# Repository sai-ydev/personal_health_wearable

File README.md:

# Wearable for Personal Health Monitoring
 
This is the repository for the Personal Health Monitoring Wearable. 

Here is the folder structure:
- **nRF54L15 Design Files** contains design files based on the nRF54L15 SoC. This couldn't be executed because of lack of availability.
- **BL54L15 Design Files** contains design files based on the BL54L15 module from [Ezurio](https://www.ezurio.com/product/bl54l15-series-bluetooth-le-80215-4-nfc).

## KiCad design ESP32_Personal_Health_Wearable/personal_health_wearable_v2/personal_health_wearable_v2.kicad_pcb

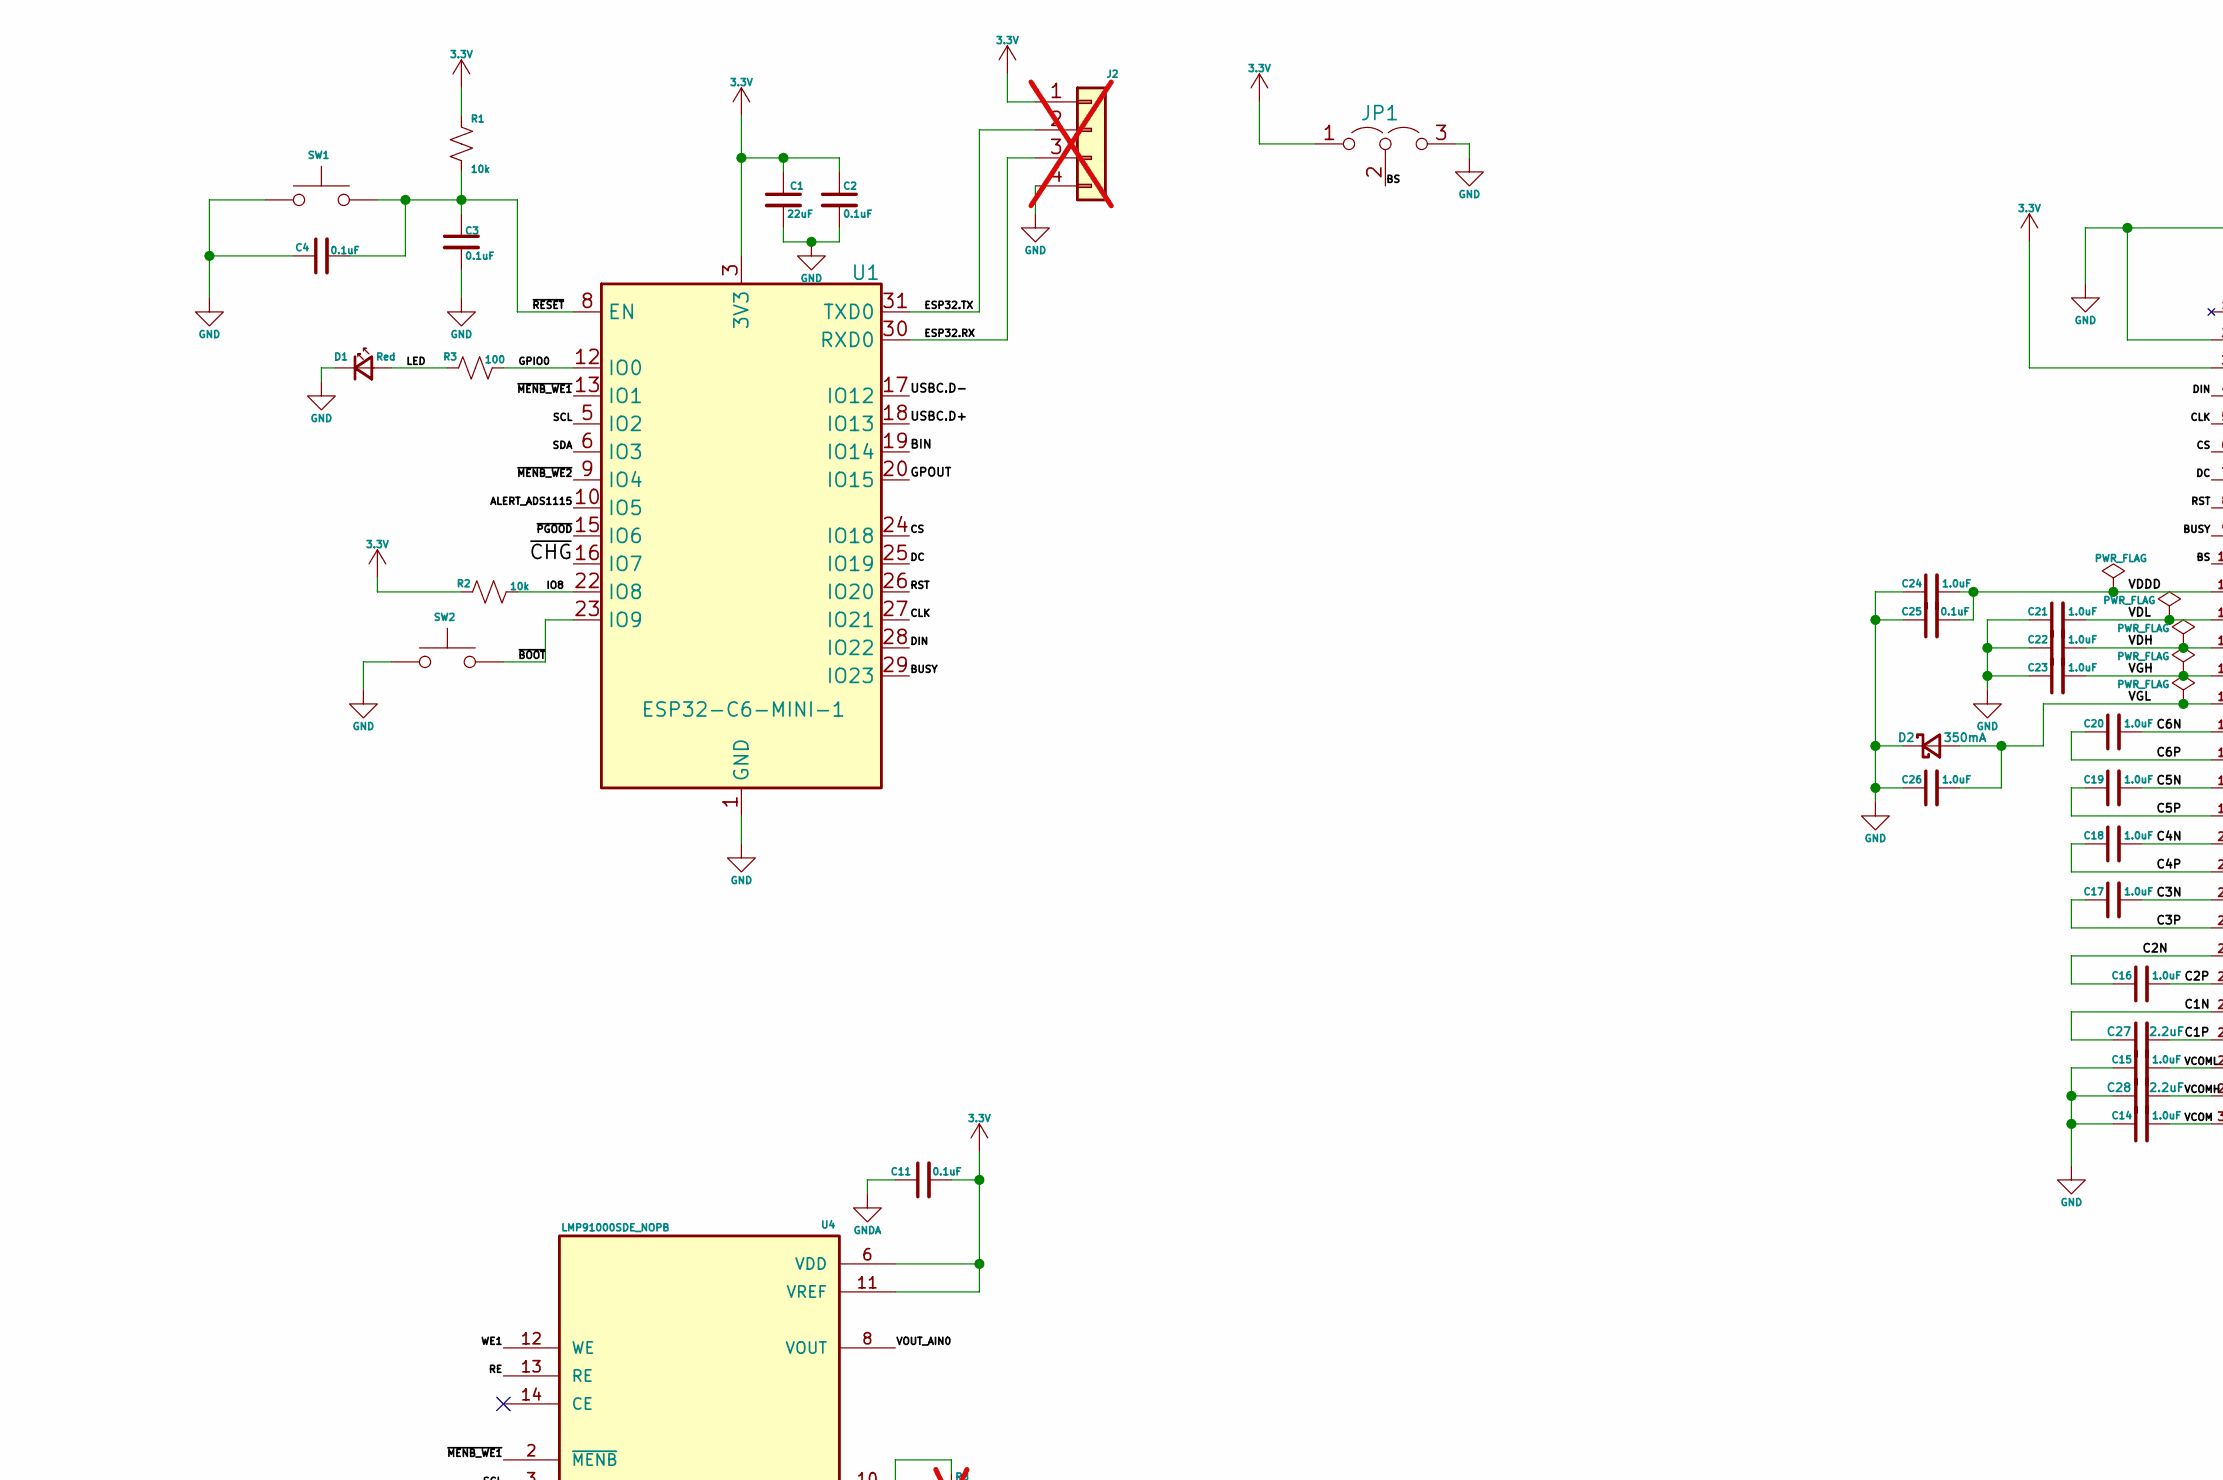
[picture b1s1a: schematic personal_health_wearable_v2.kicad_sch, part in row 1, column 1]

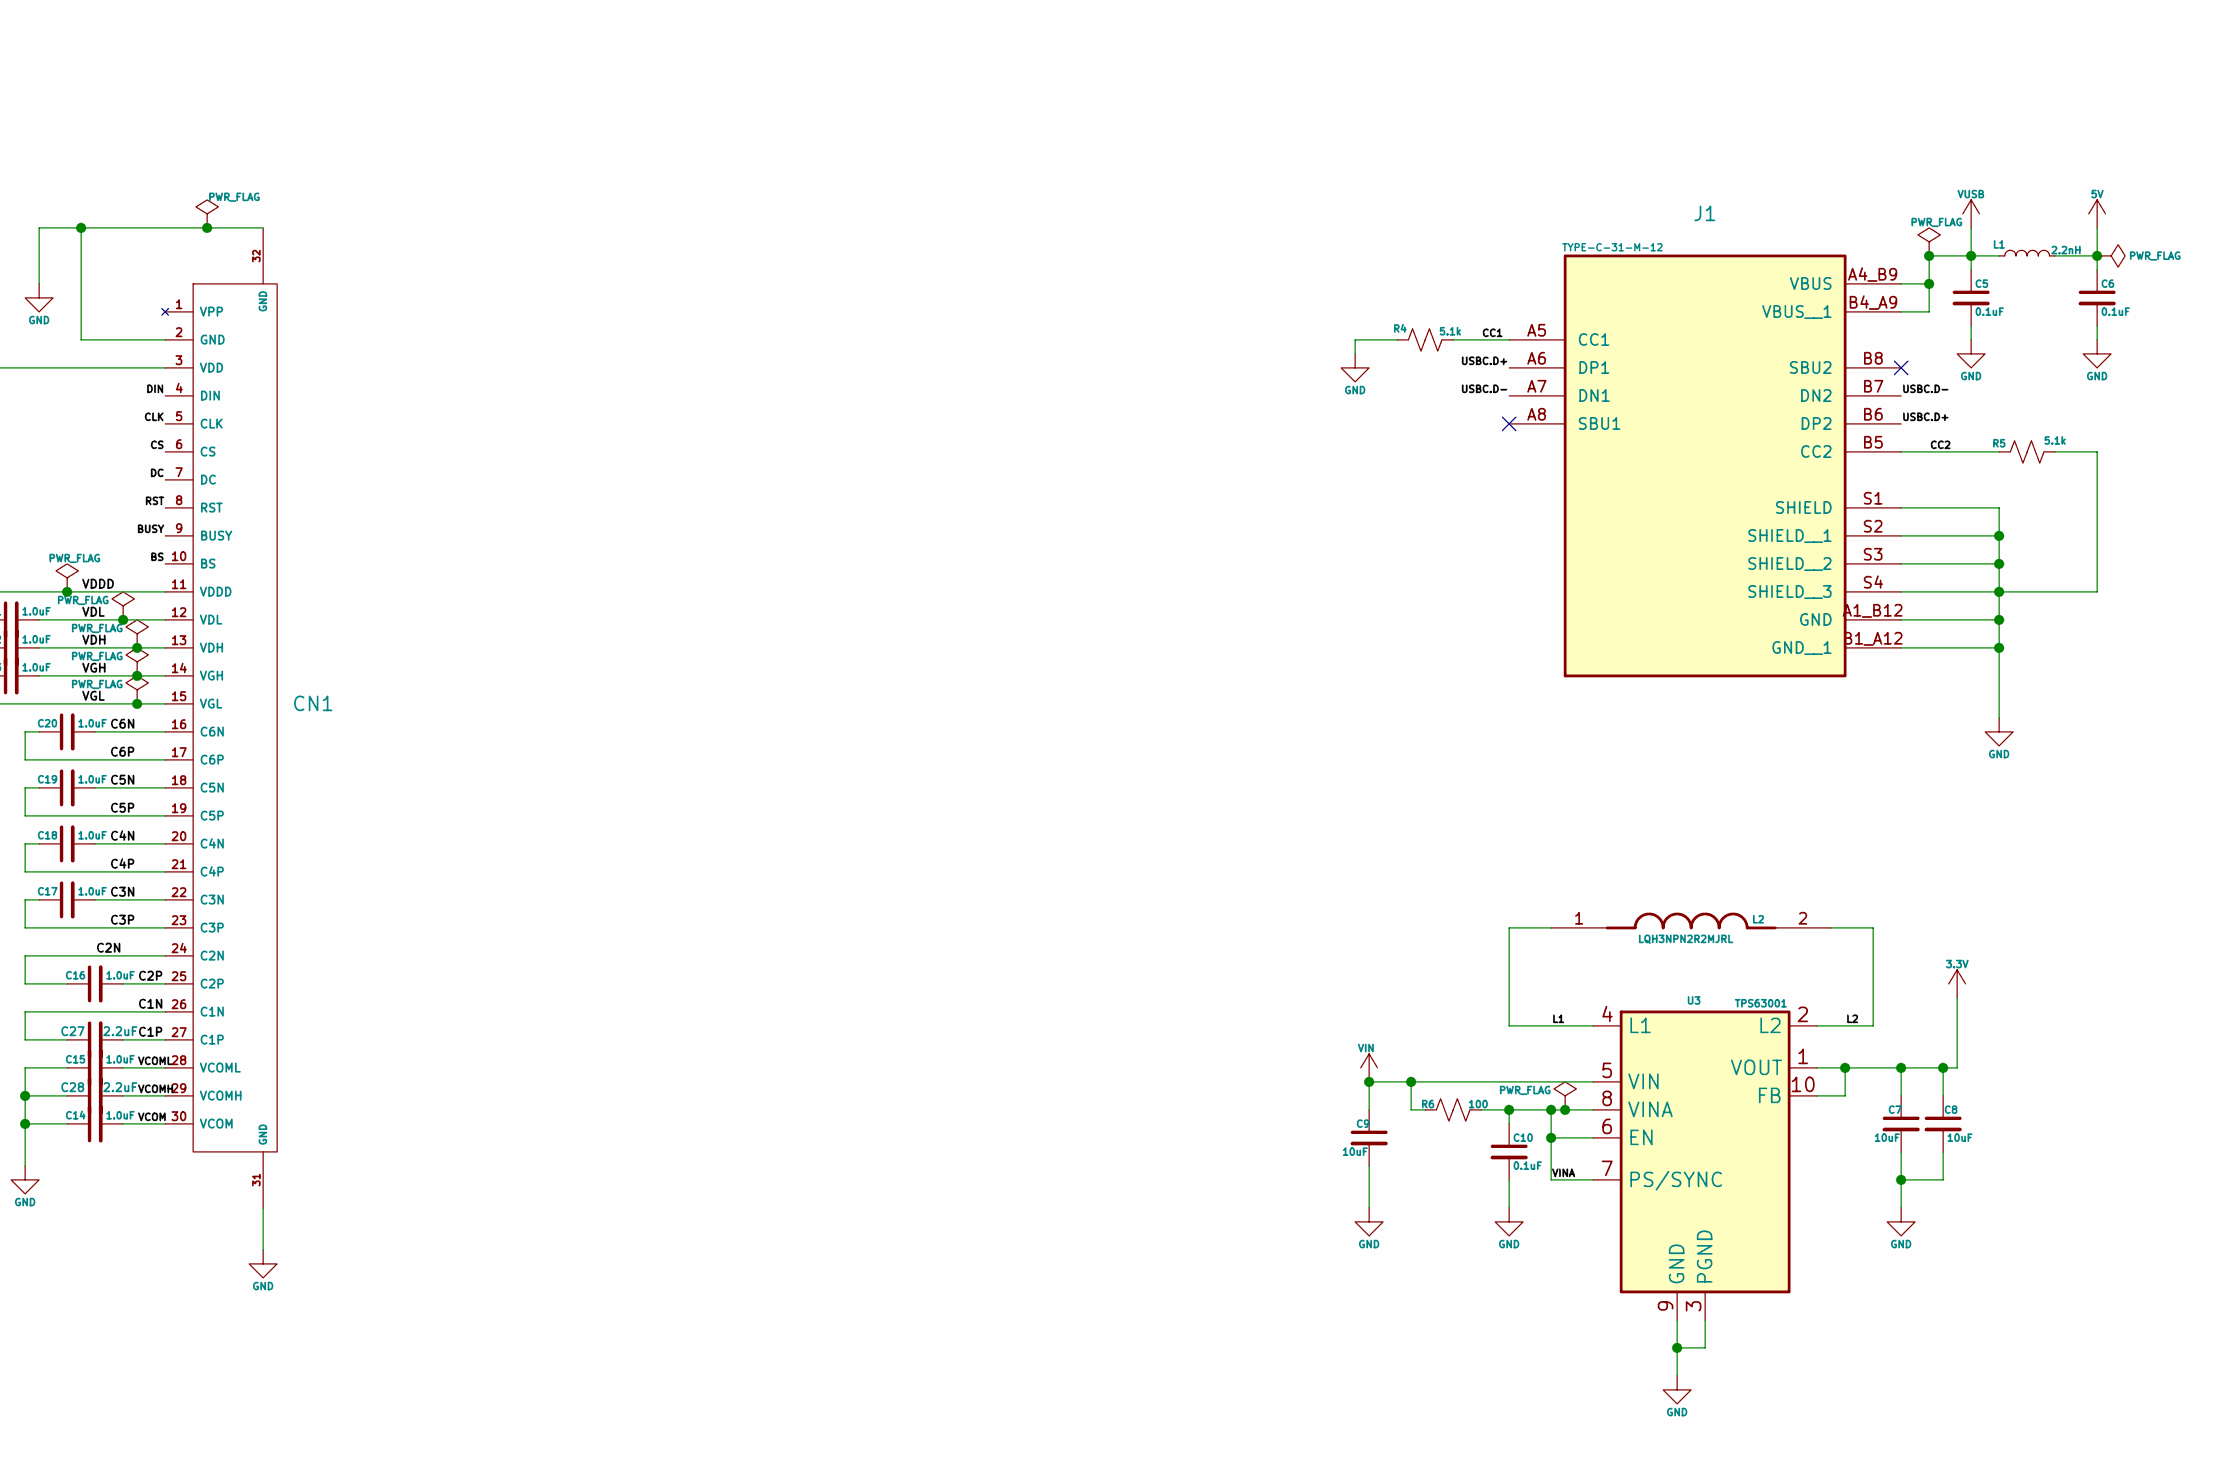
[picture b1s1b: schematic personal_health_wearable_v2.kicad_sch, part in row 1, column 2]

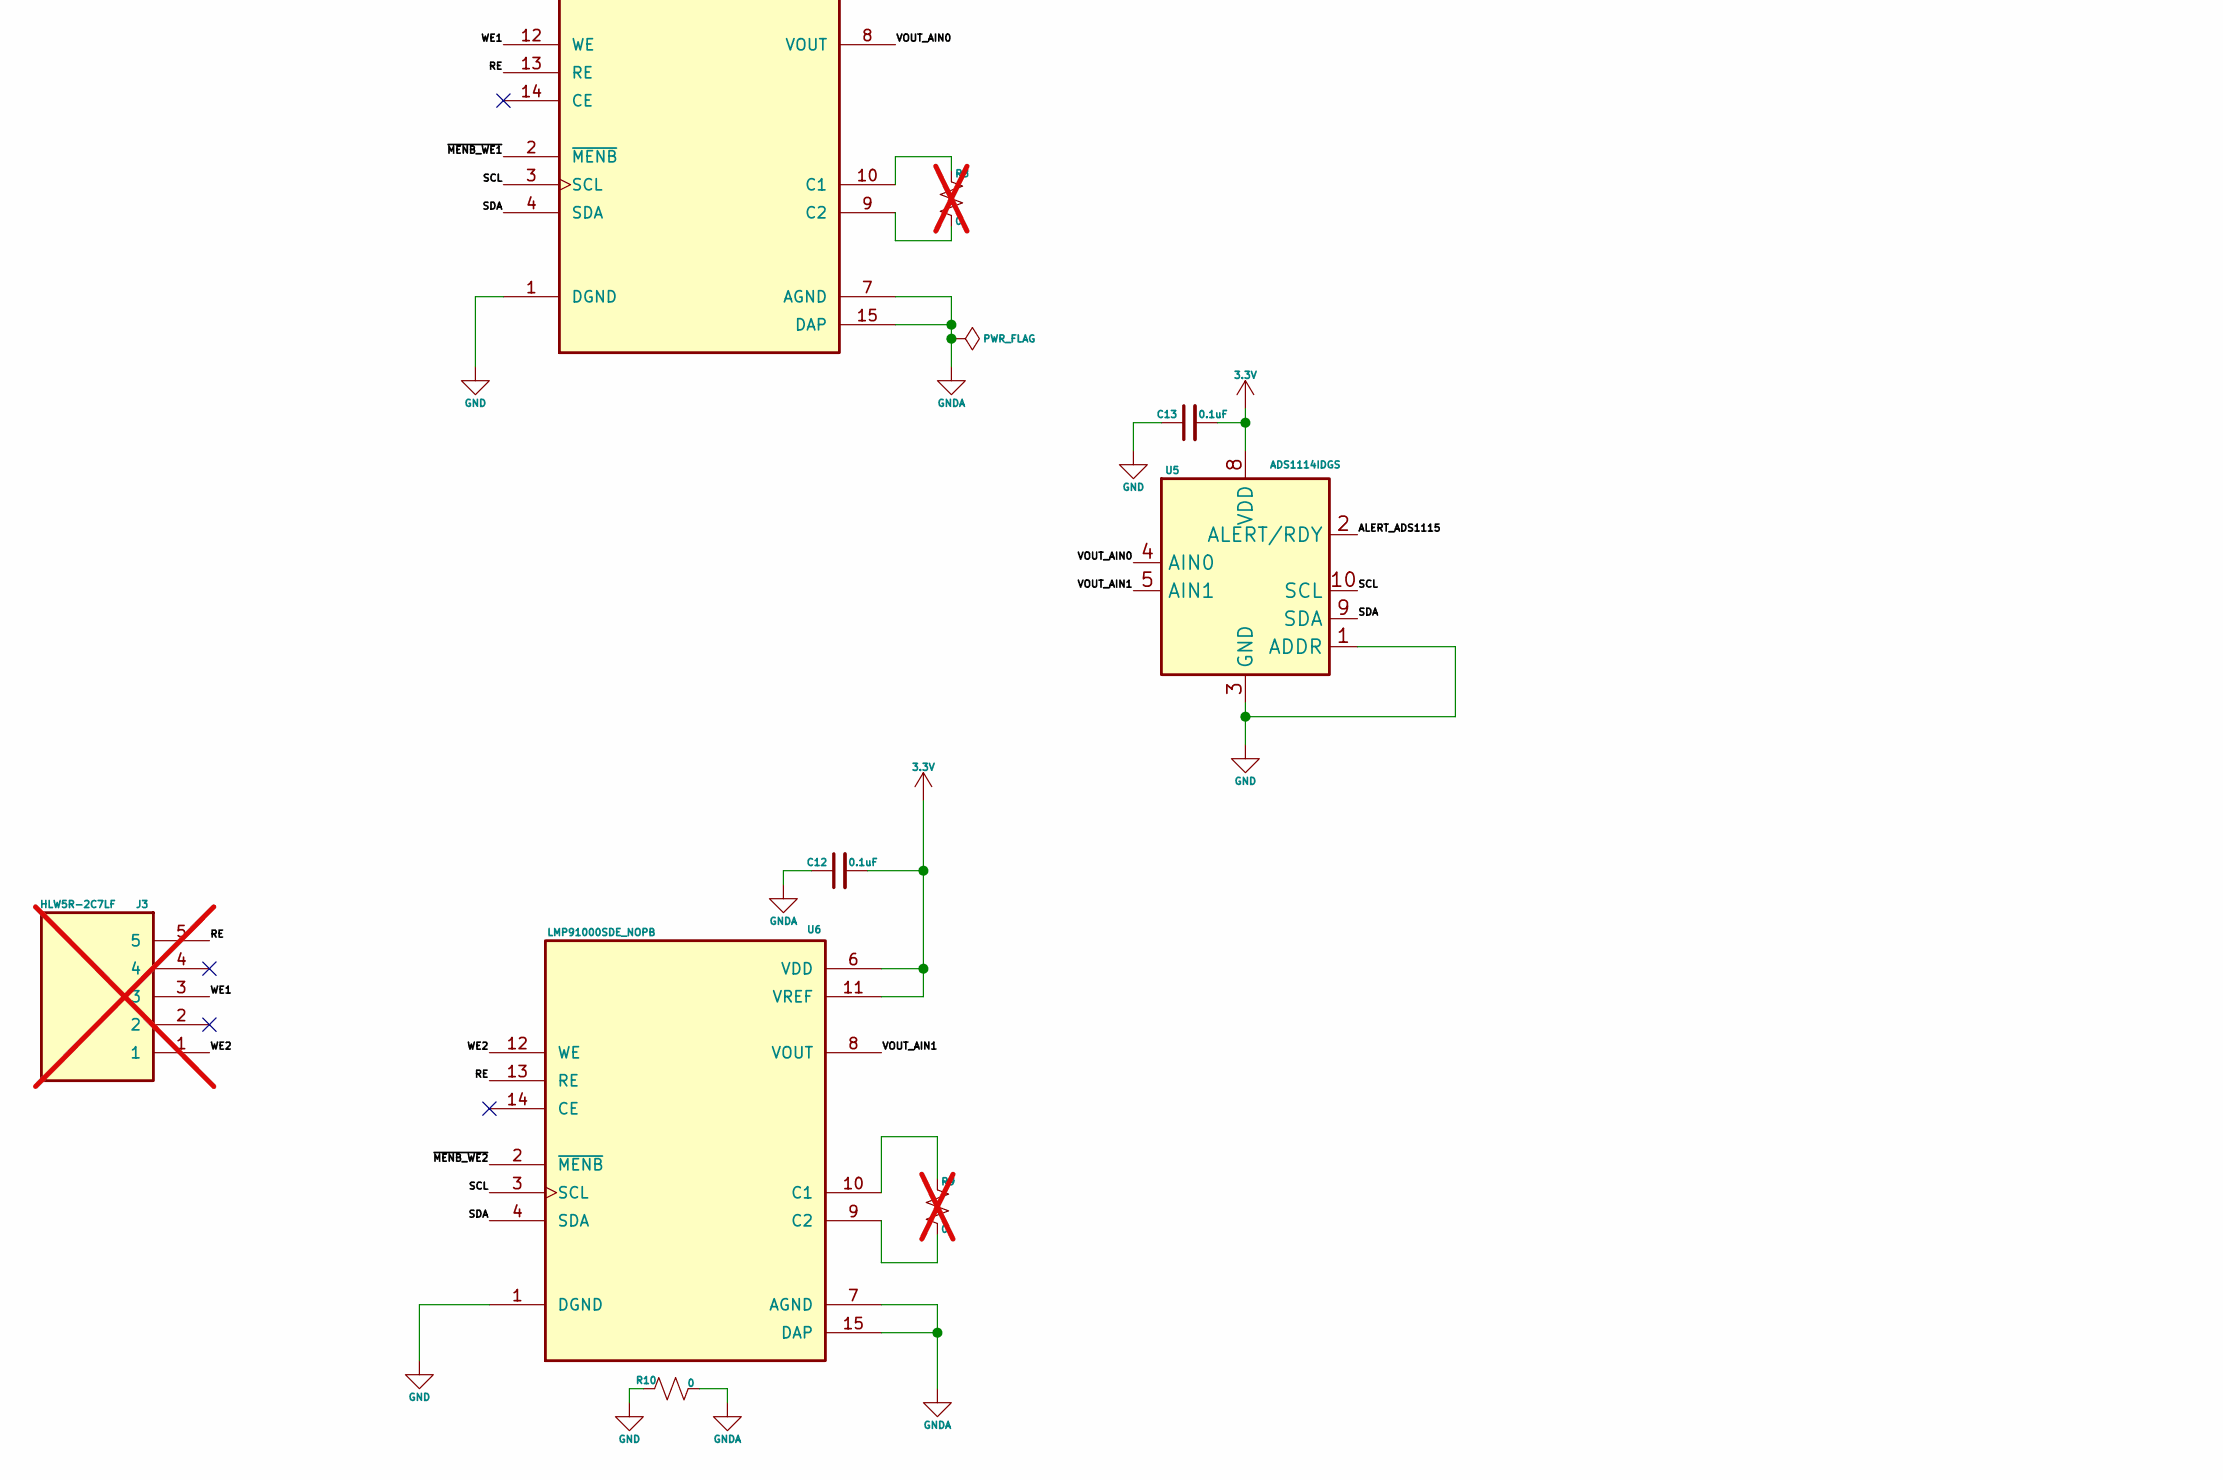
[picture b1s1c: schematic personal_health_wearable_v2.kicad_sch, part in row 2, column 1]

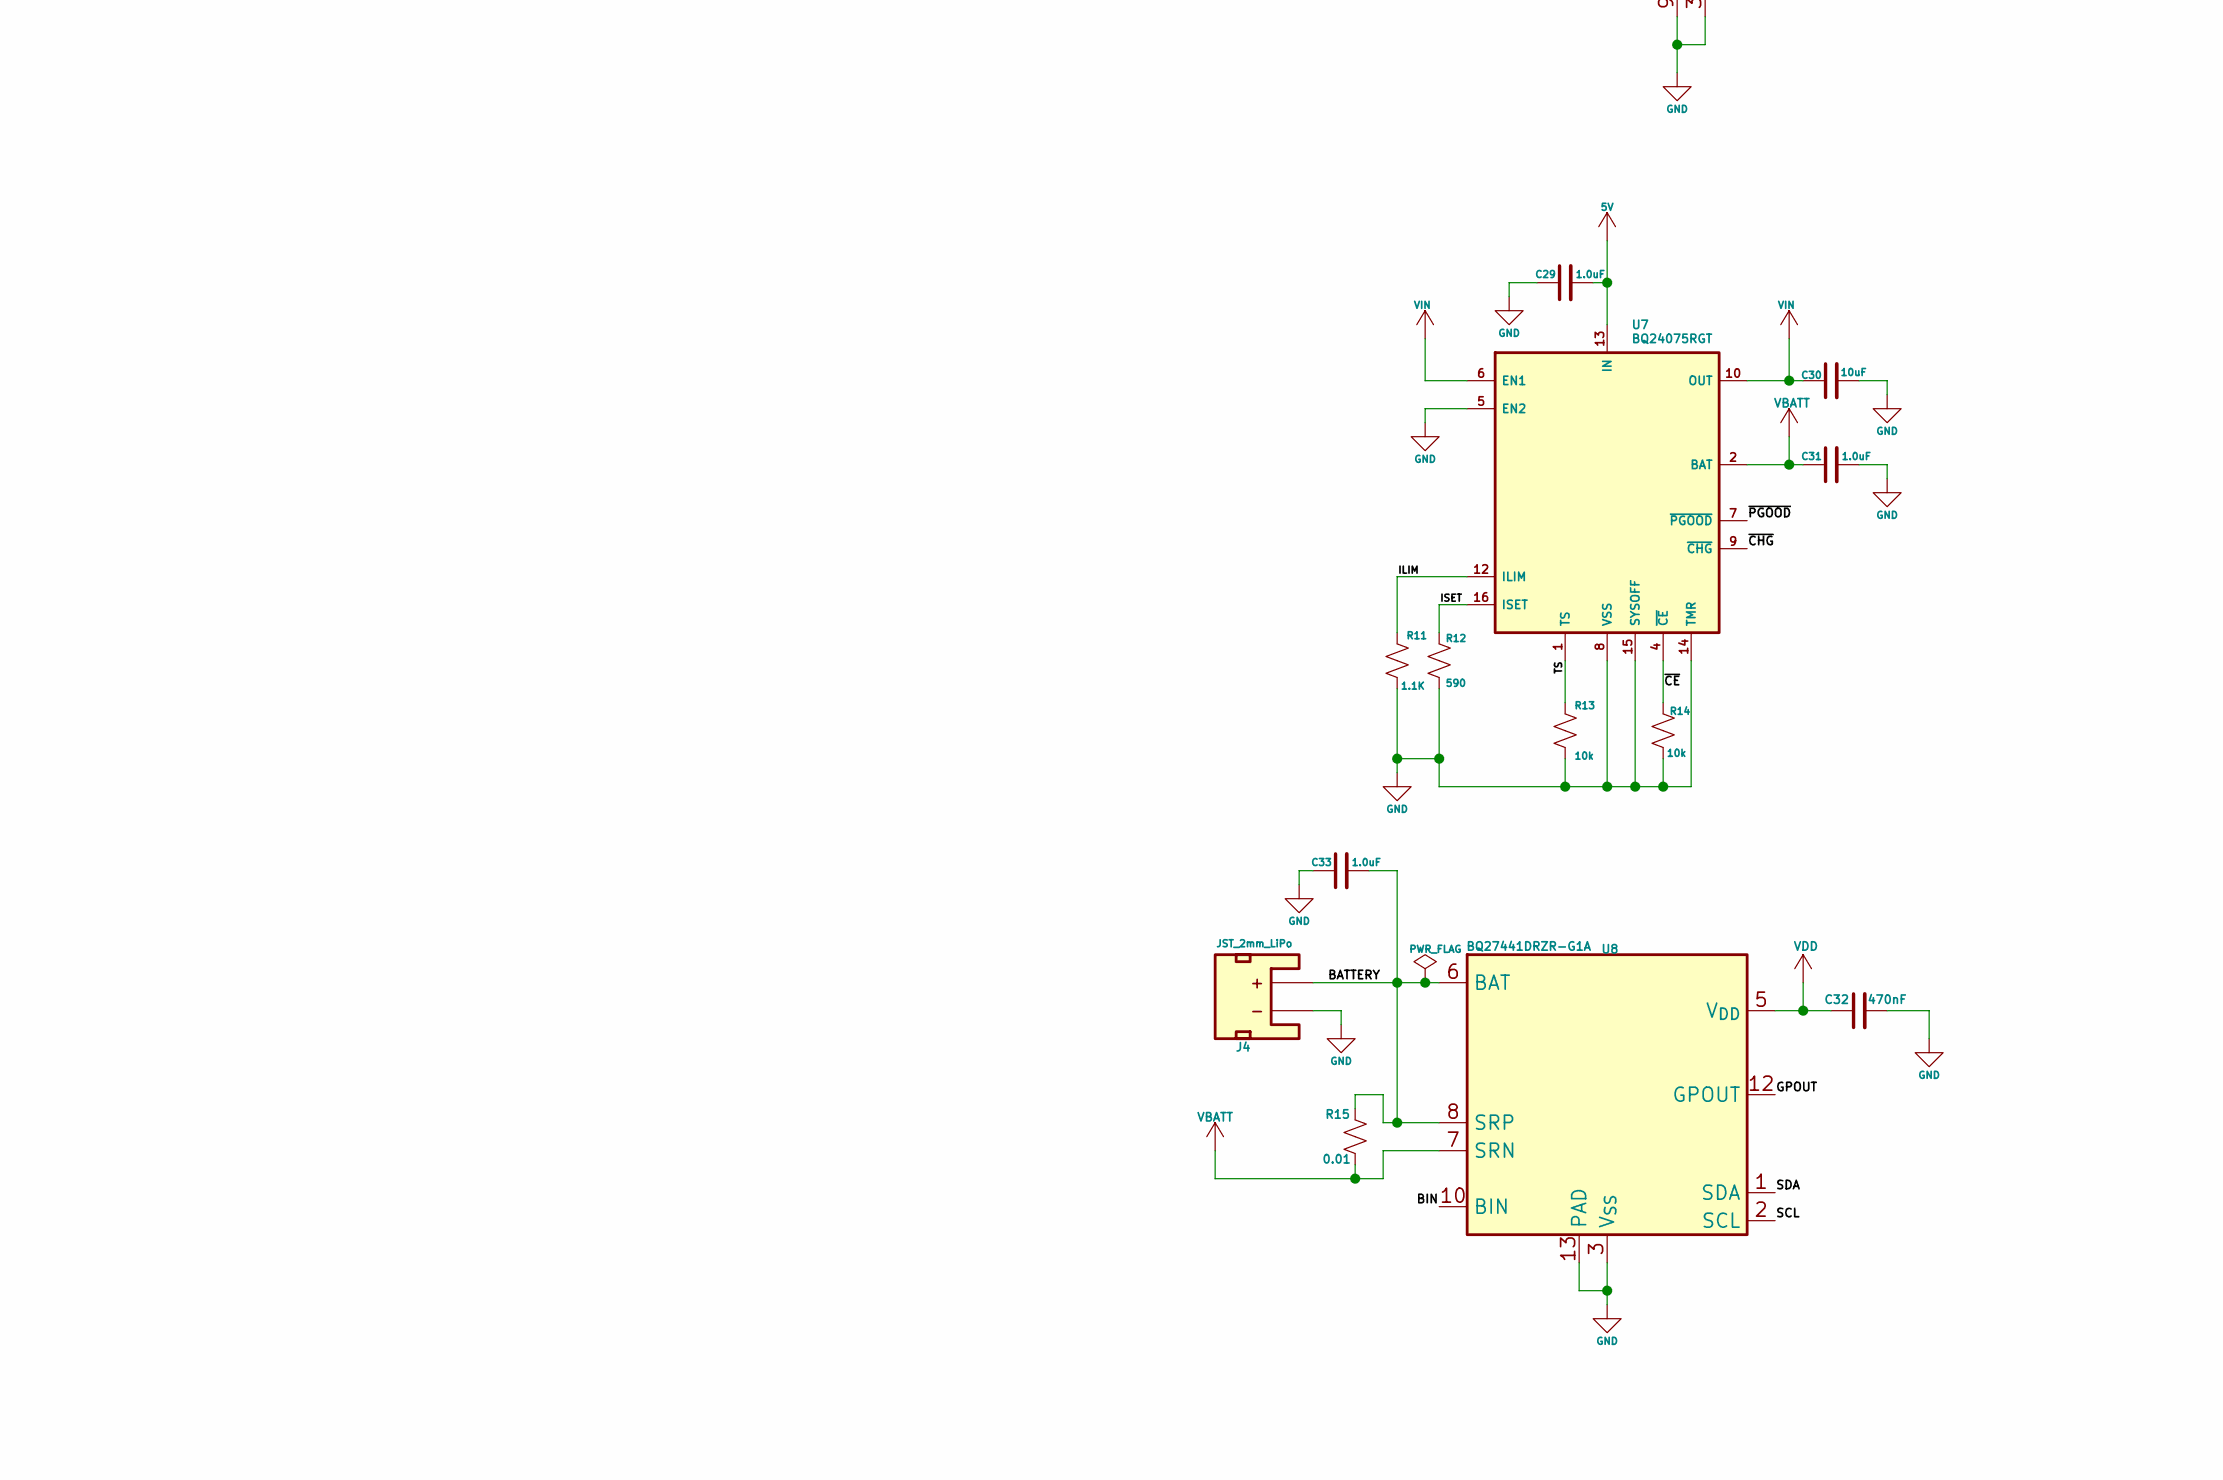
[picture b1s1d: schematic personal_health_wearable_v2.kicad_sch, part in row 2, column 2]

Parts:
C1: 22uF; C_0402_1005Metric; Voltage 6.3V; Tolerance 20%; LCSC C105226
C2, C3, C4, C5, C6, C10, C11, C12, C13, C25: 0.1uF; C_0402_1005Metric; Voltage 6.3V; Tolerance 10%; LCSC C1525
C7, C8, C9, C30: 10uF; C_0402_1005Metric; Voltage 6.3V; Tolerance 20%; LCSC C15525
C14, C15, C16, C17, C18, C19, C20, C21, C22, C23, C24, C26, C29, C31, C33: 1.0uF; C_0402_1005Metric; Voltage 16V; Tolerance 10%; LCSC C361059
C27, C28: 2.2uF; C_0402_1005Metric; Voltage 10V; Tolerance 10%; LCSC C159814
C32: 470nF; C_0402_1005Metric; Voltage 6.3V; Tolerance 10%; LCSC C47339
CN1: FPC-SMD_30P-P0.50_FH12A-30S-0.5SH; Manufacturer Part FH12A-30S-0.5SH(55); LCSC C3036214
D1: Red; LED_0402_1005Metric_Red; LCSC C74341
D2: 350mA; D_SOD-523; LCSC C154768
J1: TYPE-C-31-M-12; HRO_TYPE-C-31-M-12; PARTREV 2020.12.08; LCSC C165948
J2: Conn_01x04_RA; 1x04_P2.54mm_Header_Horizontal_SMD; not fitted
J3: HLW5R-2C7LF; AMPHENOL_HLW5R-2C7LF; PARTREV C; DigiKey_Part_Number 609-1816-ND; not fitted
J4: JST_2mm_LiPo; JST_1x02_P2.0mm_Horizontal_SMD; LCSC C295747
JP1: Jumper_3_Open; Jumper_3_NO
L1: 2.2nH; L_0402_1005Metric; LCSC C27122
L2: LQH3NPN2R2MJRL; IND_LQH3NPN2R2MJRL; PARTREV N/A; LCSC C341775
R1, R2, R13, R14: 10k; R_0402_1005Metric; LCSC C25531
R3, R6: 100; R_0402_1005Metric; LCSC C25076
R4, R5: 5.1k; R_0402_1005Metric; LCSC C25905
R8, R9: 0; R_0402_1005Metric; not fitted
R10: 0; R_0402_1005Metric; LCSC C17168
R11: 1.1K; R_0402_1005Metric; LCSC C25860
R12: 590; R_0402_1005Metric; LCSC C159007
R15: 0.01; R_0402_1005Metric; LCSC C346478
SW1, SW2: SMD_4.6x2.8mm_h1.9mm; Push_SMD_4.6x2.8mm_h1.9mm; LCSC C99271
U1: ESP32-C6-MINI-1; LCSC C5736265
U3: TPS63001; Texas_DRC0010J_ThermalVias; LCSC C28060
U4, U6: LMP91000SDE_NOPB; SON50P400X400X80-15N; PARTREV DEC 2014; LCSC C181364
U5: ADS1114IDGS; TSSOP-10_3x3mm_P0.5mm; LCSC C174291
U7: BQ24075RGT; VQFN-16-1EP_3x3mm_P0.5mm_EP1.6x1.6mm; LCSC C15464
U8: BQ27441DRZR-G1A; Texas_S-PDSO-N12; LCSC C473397

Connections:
3.3V: C1.1, C2.1, C7.1, C8.1, C11.2, C12.2, C13.2, CN1.3 (VDD), J2.1, JP1.1 (A), R1.2, R2.2, U1.3 (3V3), U3.1 (VOUT), U3.10 (FB), U4.6 (VDD), U4.11 (VREF), U5.8 (VDD), U6.6 (VDD), U6.11 (VREF)
5V: C6.1, C29.2, L1.2, U7.13 (IN)
/ALERT_ADS1115: U1.10 (IO5), U5.2 (ALERT/RDY)
/BATTERY: C33.2, J4.2 (+), R15.2, U8.6 (BAT), U8.8 (SRP)
/BIN: U1.19 (IO14), U8.10 (BIN)
/BS: CN1.10 (BS), JP1.2 (C)
/BUSY: CN1.9 (BUSY), U1.29 (IO23)
/C1N: C27.1, CN1.26 (C1N)
/C1P: C27.2, CN1.27 (C1P)
/C2N: C16.1, CN1.24 (C2N)
/C2P: C16.2, CN1.25 (C2P)
/C3N: C17.2, CN1.22 (C3N)
/C3P: C17.1, CN1.23 (C3P)
/C4N: C18.2, CN1.20 (C4N)
/C4P: C18.1, CN1.21 (C4P)
/C5N: C19.2, CN1.18 (C5N)
/C5P: C19.1, CN1.19 (C5P)
/C6N: C20.2, CN1.16 (C6N)
/C6P: C20.1, CN1.17 (C6P)
/CC1: J1.A5 (CC1), R4.2
/CC2: J1.B5 (CC2), R5.1
/CLK: CN1.5 (CLK), U1.27 (IO21)
/CS: CN1.6 (CS), U1.24 (IO18)
/DC: CN1.7 (DC), U1.25 (IO19)
/DIN: CN1.4 (DIN), U1.28 (IO22)
/ESP32.RX: J2.3, U1.30 (RXD0)
/ESP32.TX: J2.2, U1.31 (TXD0)
/GPIO0: R3.2, U1.12 (IO0)
/GPOUT: U1.20 (IO15), U8.12 (GPOUT)
/ILIM: R11.2, U7.12 (ILIM)
/IO8: R2.1, U1.22 (IO8)
/ISET: R12.2, U7.16 (ISET)
/L1: L2.1, U3.4 (L1)
/L2: L2.2, U3.2 (L2)
/LED: D1.2 (A), R3.1
/RE: J3.5, U4.13 (RE), U6.13 (RE)
/RST: CN1.8 (RST), U1.26 (IO20)
/SCL: U1.5 (IO2), U4.3 (SCL), U5.10 (SCL), U6.3 (SCL), U8.2 (SCL)
/SDA: U1.6 (IO3), U4.4 (SDA), U5.9 (SDA), U6.4 (SDA), U8.1 (SDA)
/TS: R13.2, U7.1 (TS)
/USBC.D+: J1.A6 (DP1), J1.B6 (DP2), U1.18 (IO13)
/USBC.D-: J1.A7 (DN1), J1.B7 (DN2), U1.17 (IO12)
/VCOM: C14.2, CN1.30 (VCOM)
/VCOMH: C28.2, CN1.29 (VCOMH)
/VCOML: C15.2, CN1.28 (VCOML)
/VDDD: C24.2, C25.2, CN1.11 (VDDD)
/VDH: C22.2, CN1.13 (VDH)
/VDL: C21.2, CN1.12 (VDL)
/VGH: C23.2, CN1.14 (VGH)
/VGL: C26.2, CN1.15 (VGL), D2.2 (A)
/VINA: C10.1, R6.2, U3.6 (EN), U3.7 (PS/SYNC), U3.8 (VINA)
/VOUT_AIN0: U4.8 (VOUT), U5.4 (AIN0)
/VOUT_AIN1: U5.5 (AIN1), U6.8 (VOUT)
/WE1: J3.3, U4.12 (WE)
/WE2: J3.1, U6.12 (WE)
/~BOOT: SW2.2, U1.23 (IO9)
/~CE: R14.2, U7.4 (~CE)
/~CHG: U1.16 (IO7), U7.9 (~CHG)
/~MENB_WE1: U1.13 (IO1), U4.2 (~MENB)
/~MENB_WE2: U1.9 (IO4), U6.2 (~MENB)
/~PGOOD: U1.15 (IO6), U7.7 (~PGOOD)
/~RESET: C3.1, C4.2, R1.1, SW1.2, U1.8 (EN)
GND: C1.2, C2.2, C3.2, C4.1, C5.2, C6.2, C7.2, C8.2, C9.2, C10.2, C13.1, C14.1, C15.1, C21.1, C22.1, C23.1, C24.1, C25.1, C26.1, C28.1, C29.1, C30.2, C31.2, C32.2, C33.1, CN1.2 (GND), CN1.31 (GND), CN1.32 (GND), D1.1 (K), D2.1 (K), J1.A1_B12 (GND), J1.B1_A12 (GND__1), J1.S1 (SHIELD), J1.S2 (SHIELD__1), J1.S3 (SHIELD__2), J1.S4 (SHIELD__3), J2.4, J4.1 (-), JP1.3 (B), R4.1, R5.2, R10.1, R11.1, R12.1, R13.1, R14.1, SW1.1, SW2.1, U1.1 (GND), U1.2 (GND), U1.11 (GND), U1.14 (GND), U1.36 (GND), U1.37 (GND), U1.38 (GND), U1.39 (GND), U1.40 (GND), U1.41 (GND), U1.42 (GND), U1.43 (GND), U1.44 (GND), U1.45 (GND), U1.46 (GND), U1.47 (GND), U1.48 (GND), U1.49 (GND), U1.50 (GND), U1.51 (GND), U1.52 (GND), U1.53 (GND), U3.3 (PGND), U3.9 (GND), U3.11 (PGND), U4.1 (DGND), U5.1 (ADDR), U5.3 (GND), U6.1 (DGND), U7.5 (EN2), U7.8 (VSS), U7.14 (TMR), U7.15 (SYSOFF), U7.17 (VSS), U8.3 (V_{SS}), U8.13 (PAD)
GNDA: C11.1, C12.1, R10.2, U4.7 (AGND), U4.15 (DAP), U6.7 (AGND), U6.15 (DAP)
unnamed: R8.2, U4.10 (C1)
unnamed: R8.1, U4.9 (C2)
unnamed: R9.2, U6.10 (C1)
unnamed: R9.1, U6.9 (C2)
VBATT: C31.1, R15.1, U7.2 (BAT), U7.3 (BAT), U8.7 (SRN)
VDD: C32.1, U8.5 (V_{DD})
VIN: C9.1, C30.1, R6.1, U3.5 (VIN), U7.6 (EN1), U7.10 (OUT), U7.11 (OUT)
VUSB: C5.1, J1.A4_B9 (VBUS), J1.B4_A9 (VBUS__1), L1.1

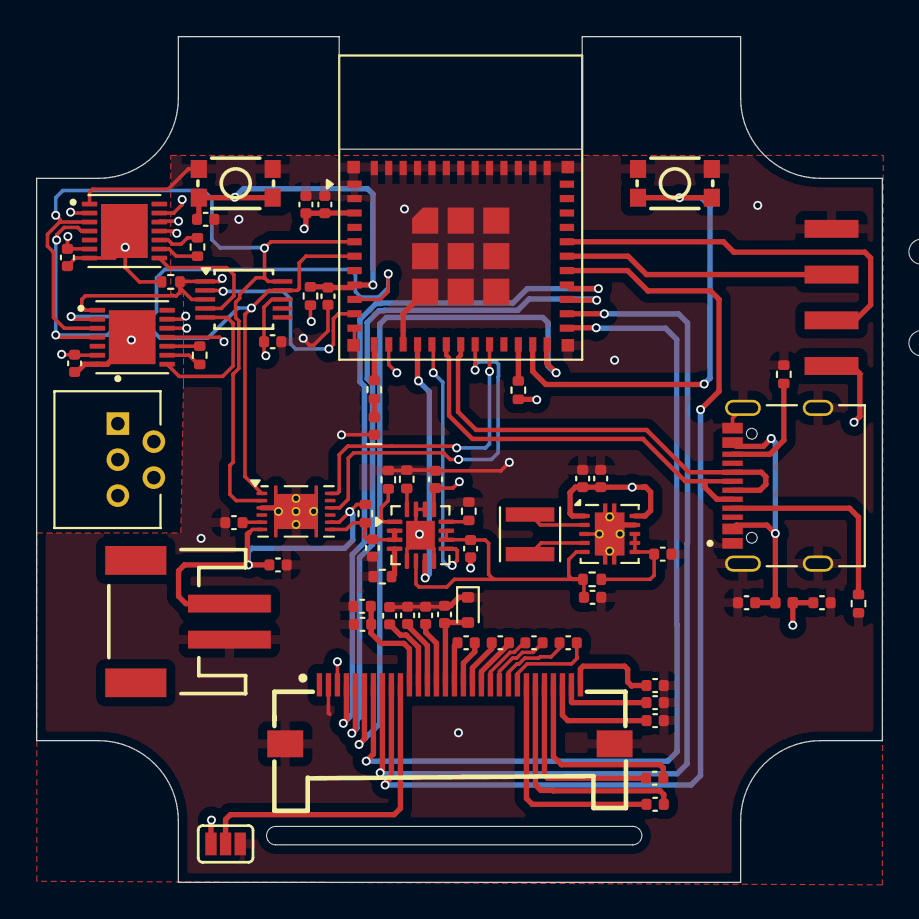
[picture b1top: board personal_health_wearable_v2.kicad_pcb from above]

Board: 4 copper layers, 47.0 x 47.0 mm, 66 parts (0 on the bottom side), 72 nets.

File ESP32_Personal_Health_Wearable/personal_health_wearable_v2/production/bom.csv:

Designator,Footprint,Quantity,Value,LCSC Part #
C1,0402,1,22uF,C105226
"C10, C11, C12, C13, C2, C25, C3, C4, C5, C6",0402,10,0.1uF,C1525
"C14, C15, C16, C17, C18, C19, C20, C21, C22, C23, C24, C26, C29, C31, C33",0402,15,1.0uF,C361059
"C27, C28",0402,2,2.2uF,C159814
"C30, C7, C8, C9",0402,4,10uF,C15525
C32,0402,1,470nF,C47339
CN1,FPC-SMD_30P-P0.50_FH12A-30S-0.5SH,1,~,C3036214
D1,0402,1,Red,C74341
D2,D_SOD-523,1,350mA,C154768
J1,HRO_TYPE-C-31-M-12,1,TYPE-C-31-M-12,C165948
J4,JST_1x02_P2.0mm_Horizontal_SMD,1,JST_2mm_LiPo,C295747
L1,0402,1,2.2nH,C27122
L2,IND_LQH3NPN2R2MJRL,1,LQH3NPN2R2MJRL,C341775
"R1, R13, R14, R2",0402,4,10k,C25531
R10,0402,1,0,C17168
R11,0402,1,1.1K,C25860
R12,0402,1,590,C159007
R15,0402,1,0.01,C346478
"R3, R6",0402,2,100,C25076
"R4, R5",0402,2,5.1k,C25905
"SW1, SW2",Push_SMD_4.6x2.8mm_h1.9mm,2,SMD_4.6x2.8mm_h1.9mm,C99271
U1,ESP32-C6-MINI-1,1,ESP32-C6-MINI-1,C5736265
U3,Texas_DRC0010J_ThermalVias,1,TPS63001,C28060
"U4, U6",SON50P400X400X80-15N,2,LMP91000SDE_NOPB,C181364
U5,TSSOP-10_3x3mm_P0.5mm,1,ADS1114IDGS,C174291
U7,VQFN-16-1EP_3x3mm_P0.5mm_EP1.6x1.6mm,1,BQ24075RGT,C15464
U8,Texas_S-PDSO-N12,1,BQ27441DRZR-G1A,C473397

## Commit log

2025-01-26 Design file check-in
2025-05-07 organizing design files
2025-05-08 checking in image for read me file
2025-05-08 Update README.md
    Included gif image
2026-03-15 Checking in v2 of wearable.
2026-03-19 TPS63001 check-in
2026-03-20 Routed i2c connections
2026-03-26 Completed schematic
2026-03-28 Completed design file, BoM, and Gerbers
